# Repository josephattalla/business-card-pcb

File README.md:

# business-card-pcb
A low power stm32 driven pcb business card powered by a coin cell battery featuring an 8x8 LED matrix and push button controllable by the stm32.

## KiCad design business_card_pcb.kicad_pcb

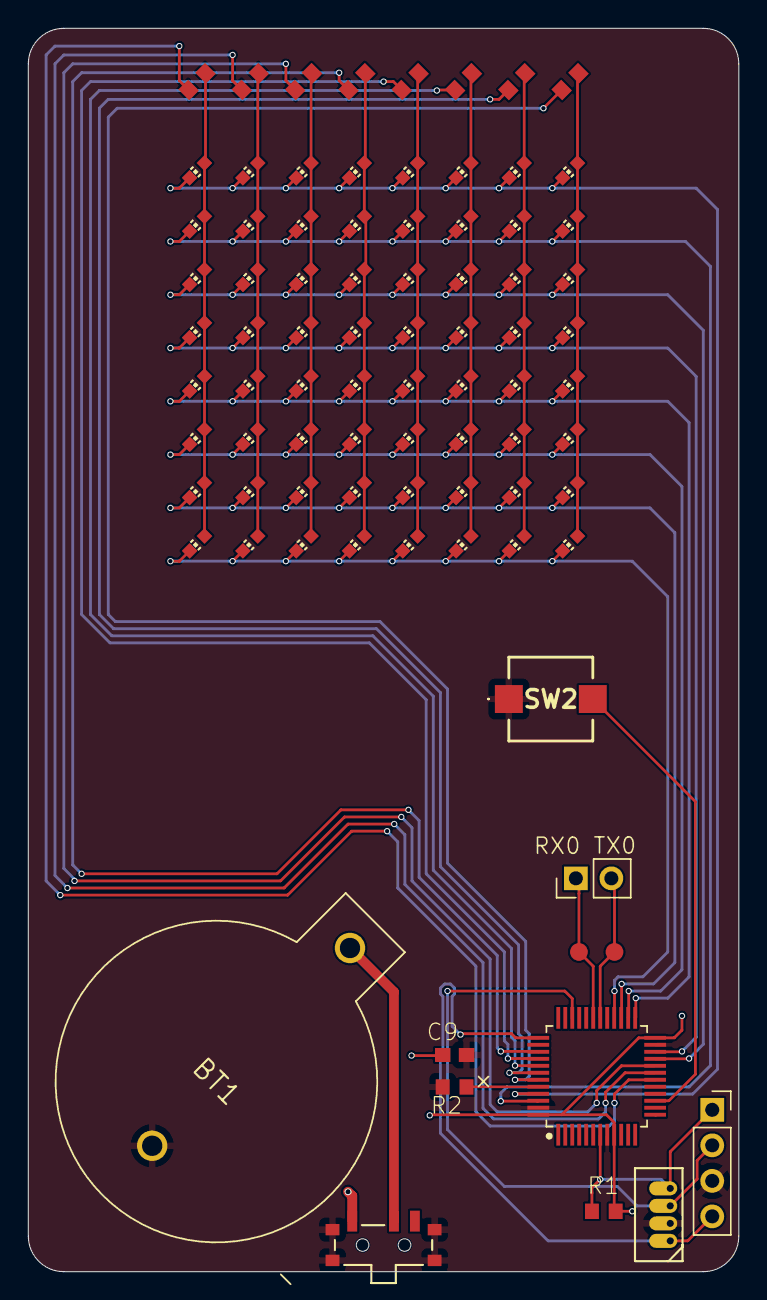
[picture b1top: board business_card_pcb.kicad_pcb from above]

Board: 2 copper layers, 50.8 x 88.9 mm, 83 parts (0 on the bottom side), 34 nets.

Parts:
BT1: Battery; BAT_BS-3
C9: 0.1uF; C0603_334
J1: Conn_01x04_Pin; PinSocket_1x04_P2.54mm_Vertical
LED1, LED2, LED3, LED4, LED5, LED6, LED7, LED8, LED9, LED10, LED11, LED12, LED13, LED14, LED15, LED16, LED17, LED18, LED19, LED20, LED21, LED22, LED23, LED24, LED25, LED26, LED27, LED28, LED29, LED30, LED31, LED32, LED33, LED34, LED35, LED36, LED37, LED38, LED39, LED40, LED41, LED42, LED43, LED44, LED45, LED46, LED47, LED48, LED49, LED50, LED51, LED52, LED53, LED54, LED55, LED56, LED57, LED58, LED59, LED60, LED61, LED62, LED63, LED64: LEDCHIP-LED0603; CHIP-LED0603_420
MP1: STM32L431CC; QFP50P900X900X160-48
PROG0: 4-PIN-1.25MM; 4-PIN-1.25MM_4492387
R1, R2: 10k; R0603_334
R3, R4, R5, R6, R7, R8, R9, R10: 500r; R0603_334
RX0: PTR1B1,27; B1,27_385
SW1: SSSS811101SW4_SSSS811101_ALPS; SW4_SSSS811101_ALPS
SW2: SW_Push; SPEH110101
TX0: PTR1B1,27; B1,27_385

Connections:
+3V3: C9.1, MP1.9, MP1.24, MP1.48, R1.2, SW1.7 (1)
/BTN1: MP1.15, SW2.2
/LED_N0: LED1.C, LED2.C, LED3.C, LED4.C, LED5.C, LED6.C, LED7.C, LED8.C, MP1.45
/LED_N1: LED9.C, LED10.C, LED11.C, LED12.C, LED13.C, LED14.C, LED15.C, LED16.C, MP1.46
/LED_N2: LED17.C, LED18.C, LED19.C, LED20.C, LED21.C, LED22.C, LED23.C, LED24.C, MP1.21
/LED_N3: LED25.C, LED26.C, LED27.C, LED28.C, LED29.C, LED30.C, LED31.C, LED32.C, MP1.22
/LED_N4: LED33.C, LED34.C, LED35.C, LED36.C, LED37.C, LED38.C, LED39.C, LED40.C, MP1.25
/LED_N5: LED41.C, LED42.C, LED43.C, LED44.C, LED45.C, LED46.C, LED47.C, LED48.C, MP1.26
/LED_N6: LED49.C, LED50.C, LED51.C, LED52.C, LED53.C, LED54.C, LED55.C, LED56.C, MP1.27
/LED_N7: LED57.C, LED58.C, LED59.C, LED60.C, LED61.C, LED62.C, LED63.C, LED64.C, MP1.28
/LED_P0: MP1.18, R3.2
/LED_P1: MP1.19, R4.2
/LED_P2: MP1.20, R5.2
/LED_P3: MP1.39, R6.2
/LED_P4: MP1.40, R7.2
/LED_P5: MP1.41, R8.2
/LED_P6: MP1.42, R9.2
/LED_P7: MP1.43, R10.2
/NRST: J1.1, MP1.7, PROG0.P$1 (4), R1.1
/SWCLK: J1.4, MP1.37, PROG0.P$4 (1)
/SWDIO: J1.2, MP1.34, PROG0.P$2 (3)
/UART_RX: MP1.31, RX0.TP
/UART_TX: MP1.30, TX0.TP
GND: BT1.-, C9.2, J1.3, MP1.8, MP1.23, MP1.47, PROG0.P$3 (2), R2.2, SW1.1 (4), SW1.2 (4), SW1.3 (4), SW1.4, SW2.1
unnamed: BT1.+, SW1.8 (2)
unnamed: LED1.A, LED9.A, LED17.A, LED25.A, LED33.A, LED41.A, LED49.A, LED57.A, R3.1
unnamed: LED2.A, LED10.A, LED18.A, LED26.A, LED34.A, LED42.A, LED50.A, LED58.A, R4.1
unnamed: LED3.A, LED11.A, LED19.A, LED27.A, LED35.A, LED43.A, LED51.A, LED59.A, R5.1
unnamed: LED4.A, LED12.A, LED20.A, LED28.A, LED36.A, LED44.A, LED52.A, LED60.A, R6.1
unnamed: LED5.A, LED13.A, LED21.A, LED29.A, LED37.A, LED45.A, LED53.A, LED61.A, R7.1
unnamed: LED6.A, LED14.A, LED22.A, LED30.A, LED38.A, LED46.A, LED54.A, LED62.A, R8.1
unnamed: LED7.A, LED15.A, LED23.A, LED31.A, LED39.A, LED47.A, LED55.A, LED63.A, R9.1
unnamed: LED8.A, LED16.A, LED24.A, LED32.A, LED40.A, LED48.A, LED56.A, LED64.A, R10.1
unnamed: MP1.44, R2.1

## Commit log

2025-08-30 Add image to README for business card PCB
    Added an image to the README for better visualization.
2025-08-30 Enhance README with push button feature
    Updated project description to include push button feature.
